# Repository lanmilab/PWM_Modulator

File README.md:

# PWM_Modulator

Analog Pulse Width Modulator. Takes analog input signal like audio or ultrasound or DC voltage and modulates into differential output signal PWM1/PWM2 suitable for H-Bridge control. 

Applications:
  - Class D Audio Power Amplifier

  - DC/DC power converter
  - LED Driver

## Signal Input Options
- **3.5mm Phono Jack J1.** This is suitable for connecting Audio signal source using Stereo Cable and 3.5mm male connector.
- **2.54mm Header J2.** Can be used to connect with another board as signal source like I2S DAC or Bluetooth Transceiver Module.
- **Potentiometer RV2.** In this case variable input is set via resistive potentiometer suitable for DC/DC  converter applications.
## Operation Modes
- **No Feedback.** R9 resistor should be populated and R15 unpopulated making feedback differential amplifier disconnected. Output pulse width is proportianal to input signal with default full scale input level of 1Vrms.
- **With Feedback.** Regulation is possible by closing negative Feedback circuit (see Class-D amplifier application) by populating R15 resistor and leaving R9 unpopulated. Feedback input connects to final regulation output (H-Bridge power stage output) through resistor divider network in order to adjust full scale of output (0-VCC) to full scale of input (1Vrms).
## Material
All parts listed in [LanmiLab_PWM_Modulator_BOM.csv](https://github.com/lanmilab/PWM_Modulator/blob/master/Production/Assembly/LanmiLab_PWM_Modulator_BOM.csv "LanmiLab_PWM_Modulator_BOM.csv"). Or use Application specific BOM from [PWM_Modulator](https://github.com/lanmilab/PWM_Modulator)/**Applications**/.
## PCB Fabrication
Send [LanmiLab_PWM_Modulator_gerbers.zip](https://github.com/lanmilab/PWM_Modulator/blob/master/Production/PCB/LanmiLab_PWM_Modulator_gerbers.zip "LanmiLab_PWM_Modulator_gerbers.zip") fabrication files to PCB Manufacturer.
## Assembly
Download and use [ibom.html](https://github.com/lanmilab/PWM_Modulator/blob/master/Production/Assembly/ibom.html "ibom.html") as soldering guide.
## Setting Frequency
Use Trimpot **RV1** to set desired PWM frequency. If oscilloscope is available use it to measure CLOCKOUT signal at P2 pin 10, otherwise use multimeter to measure RV1 resistance (between pins 1-2) and calculate frequency according:
> F=R7/(R6*(RV1+R5)*C)/4.

<a href="https://twitter.com/lanmiLab">twitter.com/lanmiLab</a>

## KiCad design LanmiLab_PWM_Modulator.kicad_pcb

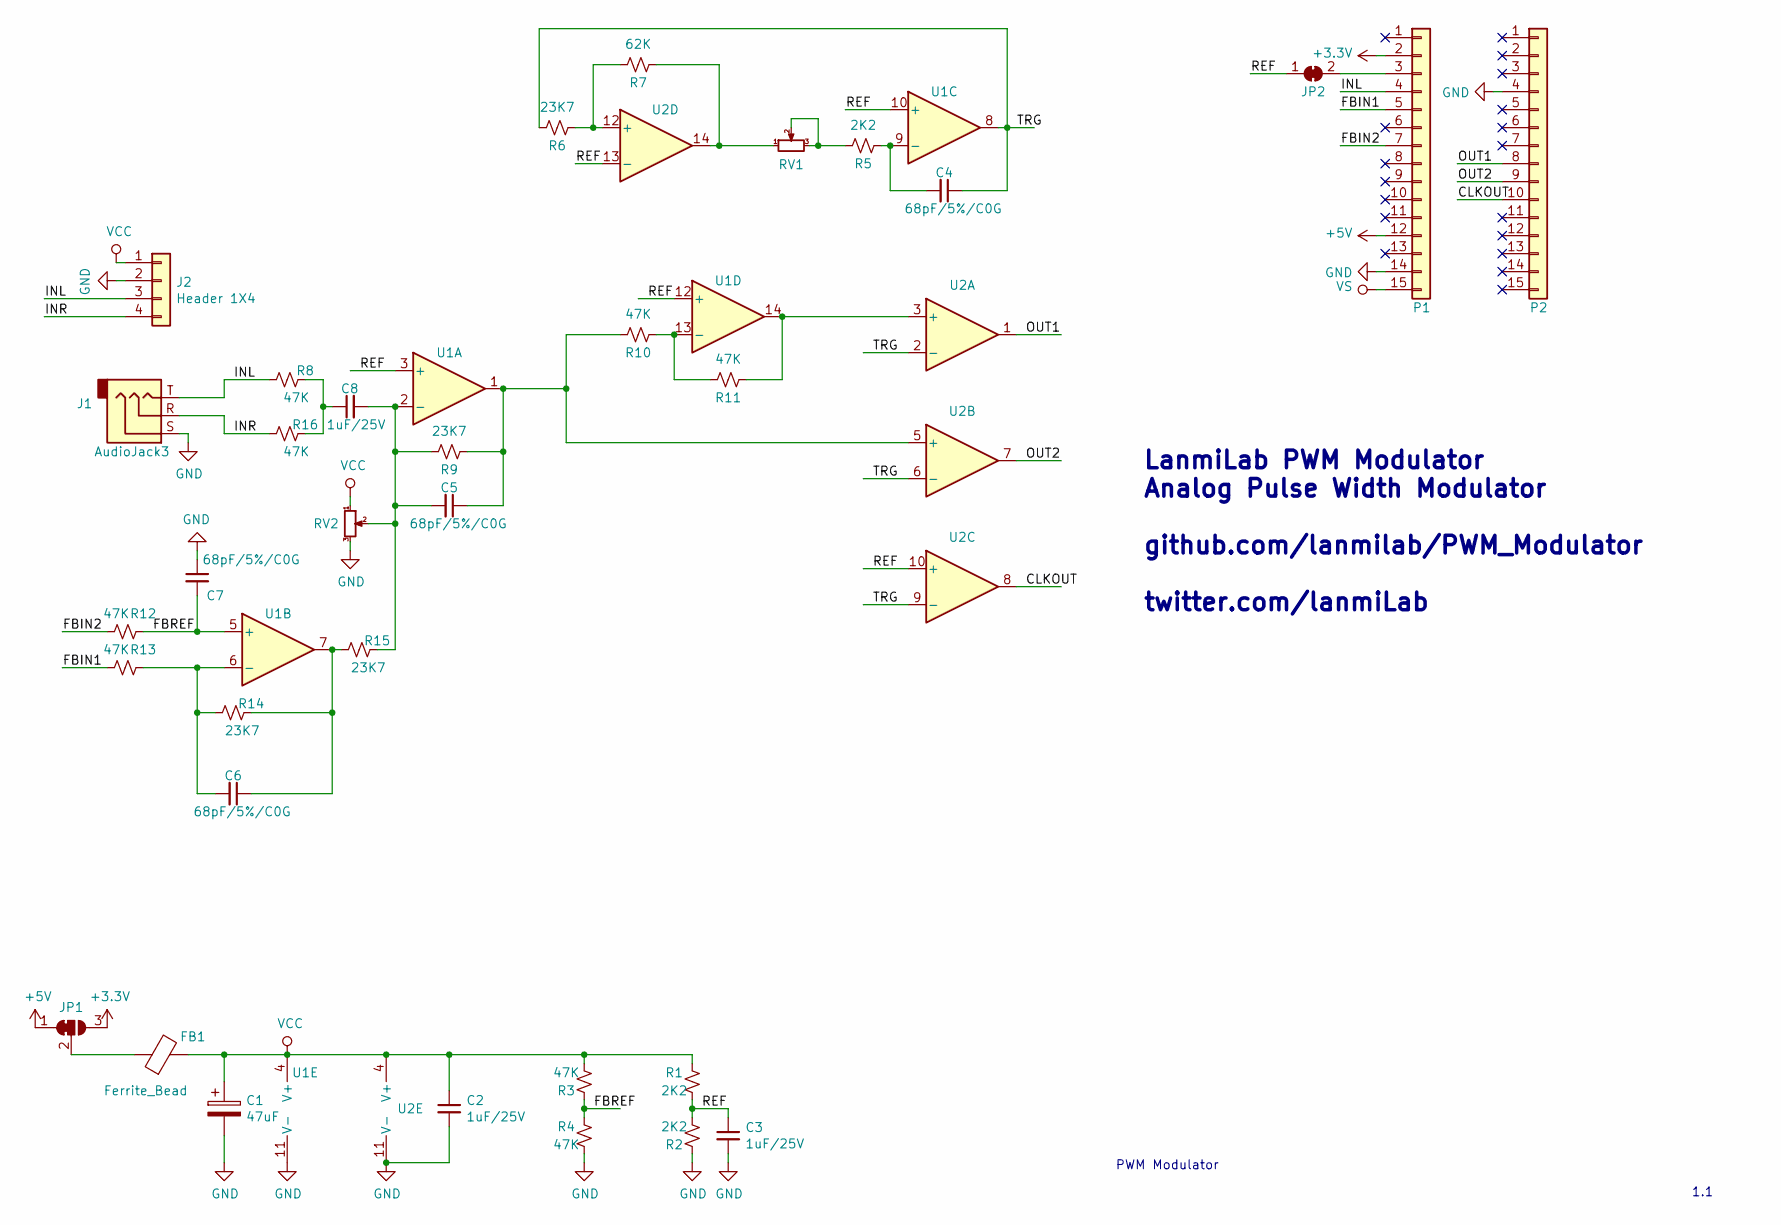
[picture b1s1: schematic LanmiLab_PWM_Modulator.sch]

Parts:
C1: 47uF; C_Radial_D4.0mm_H7.0mm_P1.50mm; Part Number ECEA0JKA470
C2, C3, C8: 1uF/25V; C_Disc_D3.8mm_W2.6mm_P2.50mm; Part Number C315C105K3R5TA
C4, C5, C6, C7: 68pF/5%/C0G; C_Disc_D3.4mm_W2.1mm_P2.50mm; Part Number K680J15C0GF53L2
FB1: Ferrite_Bead; R_Axial_DIN0309_L9.0mm_D3.2mm_P2.54mm_Vertical; Part Number BL02RN1R2M2B
J1: AudioJack3; FC68131CLIFF; Part Number FC68131
J2: Header 1X4; PinHeader_1x04_P2.54mm_Vertical
JP1: SolderJumper_3_Bridged12; SolderJumper-3_P1.3mm_Bridged12_RoundedPad1.0x1.5mm_NumberL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
JP2: SolderJumper_2_Bridged; SolderJumper-2_P1.3mm_Bridged_RoundedPad1.0x1.5mm
P1, P2: Conn_01x15; PinHeader_1x15_P2.54mm_Vertical; Part Number 61301511121
R1, R2, R5: 2K2; R_Axial_DIN0204_L3.6mm_D1.6mm_P1.90mm_Vertical; Part Number LR0204F2K2
R3, R4, R8, R10, R11, R12, R13, R16: 47K; R_Axial_DIN0204_L3.6mm_D1.6mm_P1.90mm_Vertical; Part Number LR0204F47K
R6, R9: 23K7; R_Axial_DIN0204_L3.6mm_D1.6mm_P1.90mm_Vertical; Part Number MRS25000C2372FCT00
R7: 62K; R_Axial_DIN0204_L3.6mm_D1.6mm_P1.90mm_Vertical; Part Number LR0204F62K
R14, R15: 23K7; R_Axial_DIN0204_L3.6mm_D1.6mm_P1.90mm_Vertical; Part Number MRS25000C3092FCT00
RV1: Trimpot 12 turns; Potentiometer_Bourns_3266Y_Vertical; Part Number 3266W-1-104LF
RV2: R_POT_Small; Potentiometer_Omeg_PC16BU_Horizontal; Part Number PDB181-K220K-103B
U1: Quad Opamp; DIP-14_W7.62mm; Part Number LM6144BIN/NOPB
U2: Quad Comparator; DIP-14_W7.62mm; Part Number MAX944CPD+

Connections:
+3V3: JP1.3 (B), P1.2
+5V: JP1.1 (A), P1.12
/CLKOUT: P2.10, U2.8
/FBIN1: P1.5, R13.2
/FBIN2: P1.7, R12.2
/FBREF: C7.2, R3.1, R4.1, R12.1, U1.5 (+)
/INL: J1.T, J2.3, P1.4, R8.1
/INR: J1.R, J2.4, R16.1
/OUT1: P2.8, U2.1
/OUT2: P2.9, U2.7
/REF: C3.1, JP2.1 (A), R1.2, R2.2, U1.3 (+), U1.10 (+), U1.12 (+), U2.10 (+), U2.13 (-)
/TRG: C4.1, R6.2, U1.8, U2.2 (-), U2.6 (-), U2.9 (-)
GND: C1.2, C2.2, C3.2, C7.1, J1.S, J2.2, P1.14, P2.4, R2.1, R4.2, RV2.3, U1.11 (V-), U2.11 (V-)
unnamed: C4.2, R5.1, U1.9 (-)
unnamed: C5.1, R9.1, R10.2, U1.1, U2.5 (+)
unnamed: C5.2, C8.2, R9.2, R15.2, RV2.2, U1.2 (-)
unnamed: C6.1, R14.2, R15.1, U1.7
unnamed: C6.2, R13.1, R14.1, U1.6 (-)
unnamed: C8.1, R8.2, R16.2
unnamed: FB1.1, JP1.2 (C)
unnamed: JP2.2 (B), P1.3
unnamed: R5.2, RV1.2, RV1.3
unnamed: R6.1, R7.2, U2.12 (+)
unnamed: R7.1, RV1.1, U2.14
unnamed: R10.1, R11.2, U1.13 (-)
unnamed: R11.1, U1.14, U2.3 (+)
VCC: C1.1, C2.1, FB1.2, J2.1, R1.1, R3.2, RV2.1, U1.4 (V+), U2.4 (V+)
VS: P1.15

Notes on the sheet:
PWM Modulator
1.1
LanmiLab PWM Modulator Analog Pulse Width Modulator github.com/lanmilab/PWM_Modulator twitter.com/lanmiLab

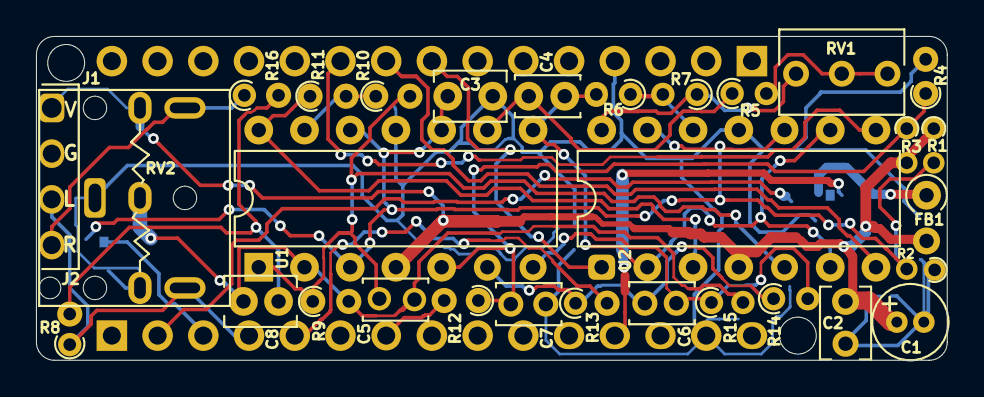
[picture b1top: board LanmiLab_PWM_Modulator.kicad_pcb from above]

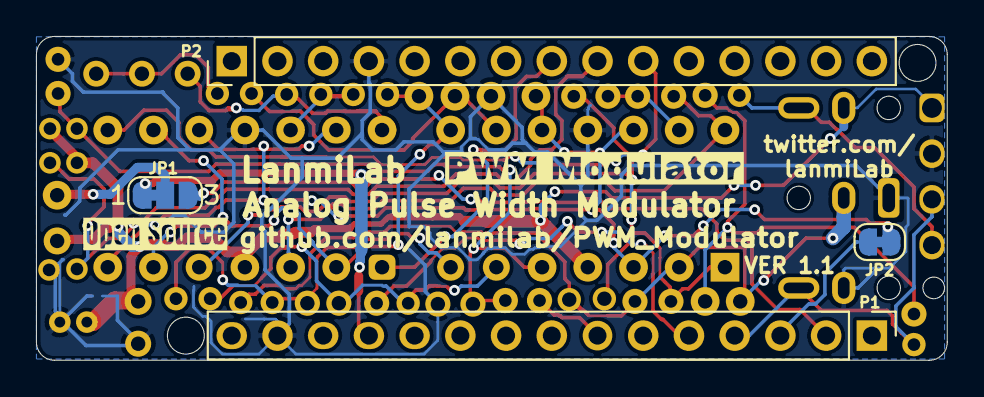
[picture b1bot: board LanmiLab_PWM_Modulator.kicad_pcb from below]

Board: 2 copper layers, 50.6 x 18.0 mm, 35 parts (4 on the bottom side), 27 nets.

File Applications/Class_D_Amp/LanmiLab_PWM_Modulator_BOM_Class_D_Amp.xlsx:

Reference | Quantity | Value | Part Number Farnell | Part Number Mouser | Note
C1 | 1 | 47uF | ECEA0JKA470 | ECE-A0JKA470
C3 C2 C8 | 3 | 1uF/25V | C315C105K3R5TA | C315C105K3R5TA
C5 C7 C4 C6 | 4 | 68pF/5%/C0G | K680J15C0GF53L2 | K680J15C0GF5TL2
FB1 | 1 | Ferrite_Bead | BL02RN1R2M2B | BL02RN1R2M2B
J1 | 1 | AudioJack3 | FC68131 | SJ1-3523N
P1 P2 | 2 | Conn_01x15 | 61301511121 | 61301511121
R12 R13 R4 R3 R10 R11 R8 R16 | 8 | 47K | LR0204F47K | MFR-12FTF52-47K
R5 R2 R1 | 3 | 2K2 | LR0204F2K2 | LR0204F2K2
R6 R15 R14 R9 | 4 | 23K7 | MRS25000C2372FCT00 | MRS25000C2372FCT00 | R9 Not populated in Feedback variant, R15 Not populated in No Feedback variant
R7 | 1 | 62K | LR0204F62K | LR0204F62K
RV1 | 1 | Trimpot 12 turns | 3266W-1-104LF | 3266W-1-104LF
U1 | 1 | Quad Opamp | LM6144BIN/NOPB | LM6144BIN/NOPB
U2 | 1 | Quad Comparator | MAX944CPD+ | MAX944CPD+

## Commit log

2020-03-03 Create Licence
2020-03-04 Class-D Amplifier application diagram
2020-03-04 Update with application diagram for Class D Power Amplifier
2020-03-31 Update Licence
2020-03-31 Gerbers Version 1.1 update
2020-03-31 Version 1.1 Update
2020-03-31 Links update
2020-03-31 Version 1.1 Update
    Update to version 1.1 based on first prototype test.
2020-04-01 Part list for Class-D Amp Application
2020-04-04 Description added
